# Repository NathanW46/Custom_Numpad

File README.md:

Custom numpad with 2 encoders and 18 Choc switches.
My first micro-electronics project.

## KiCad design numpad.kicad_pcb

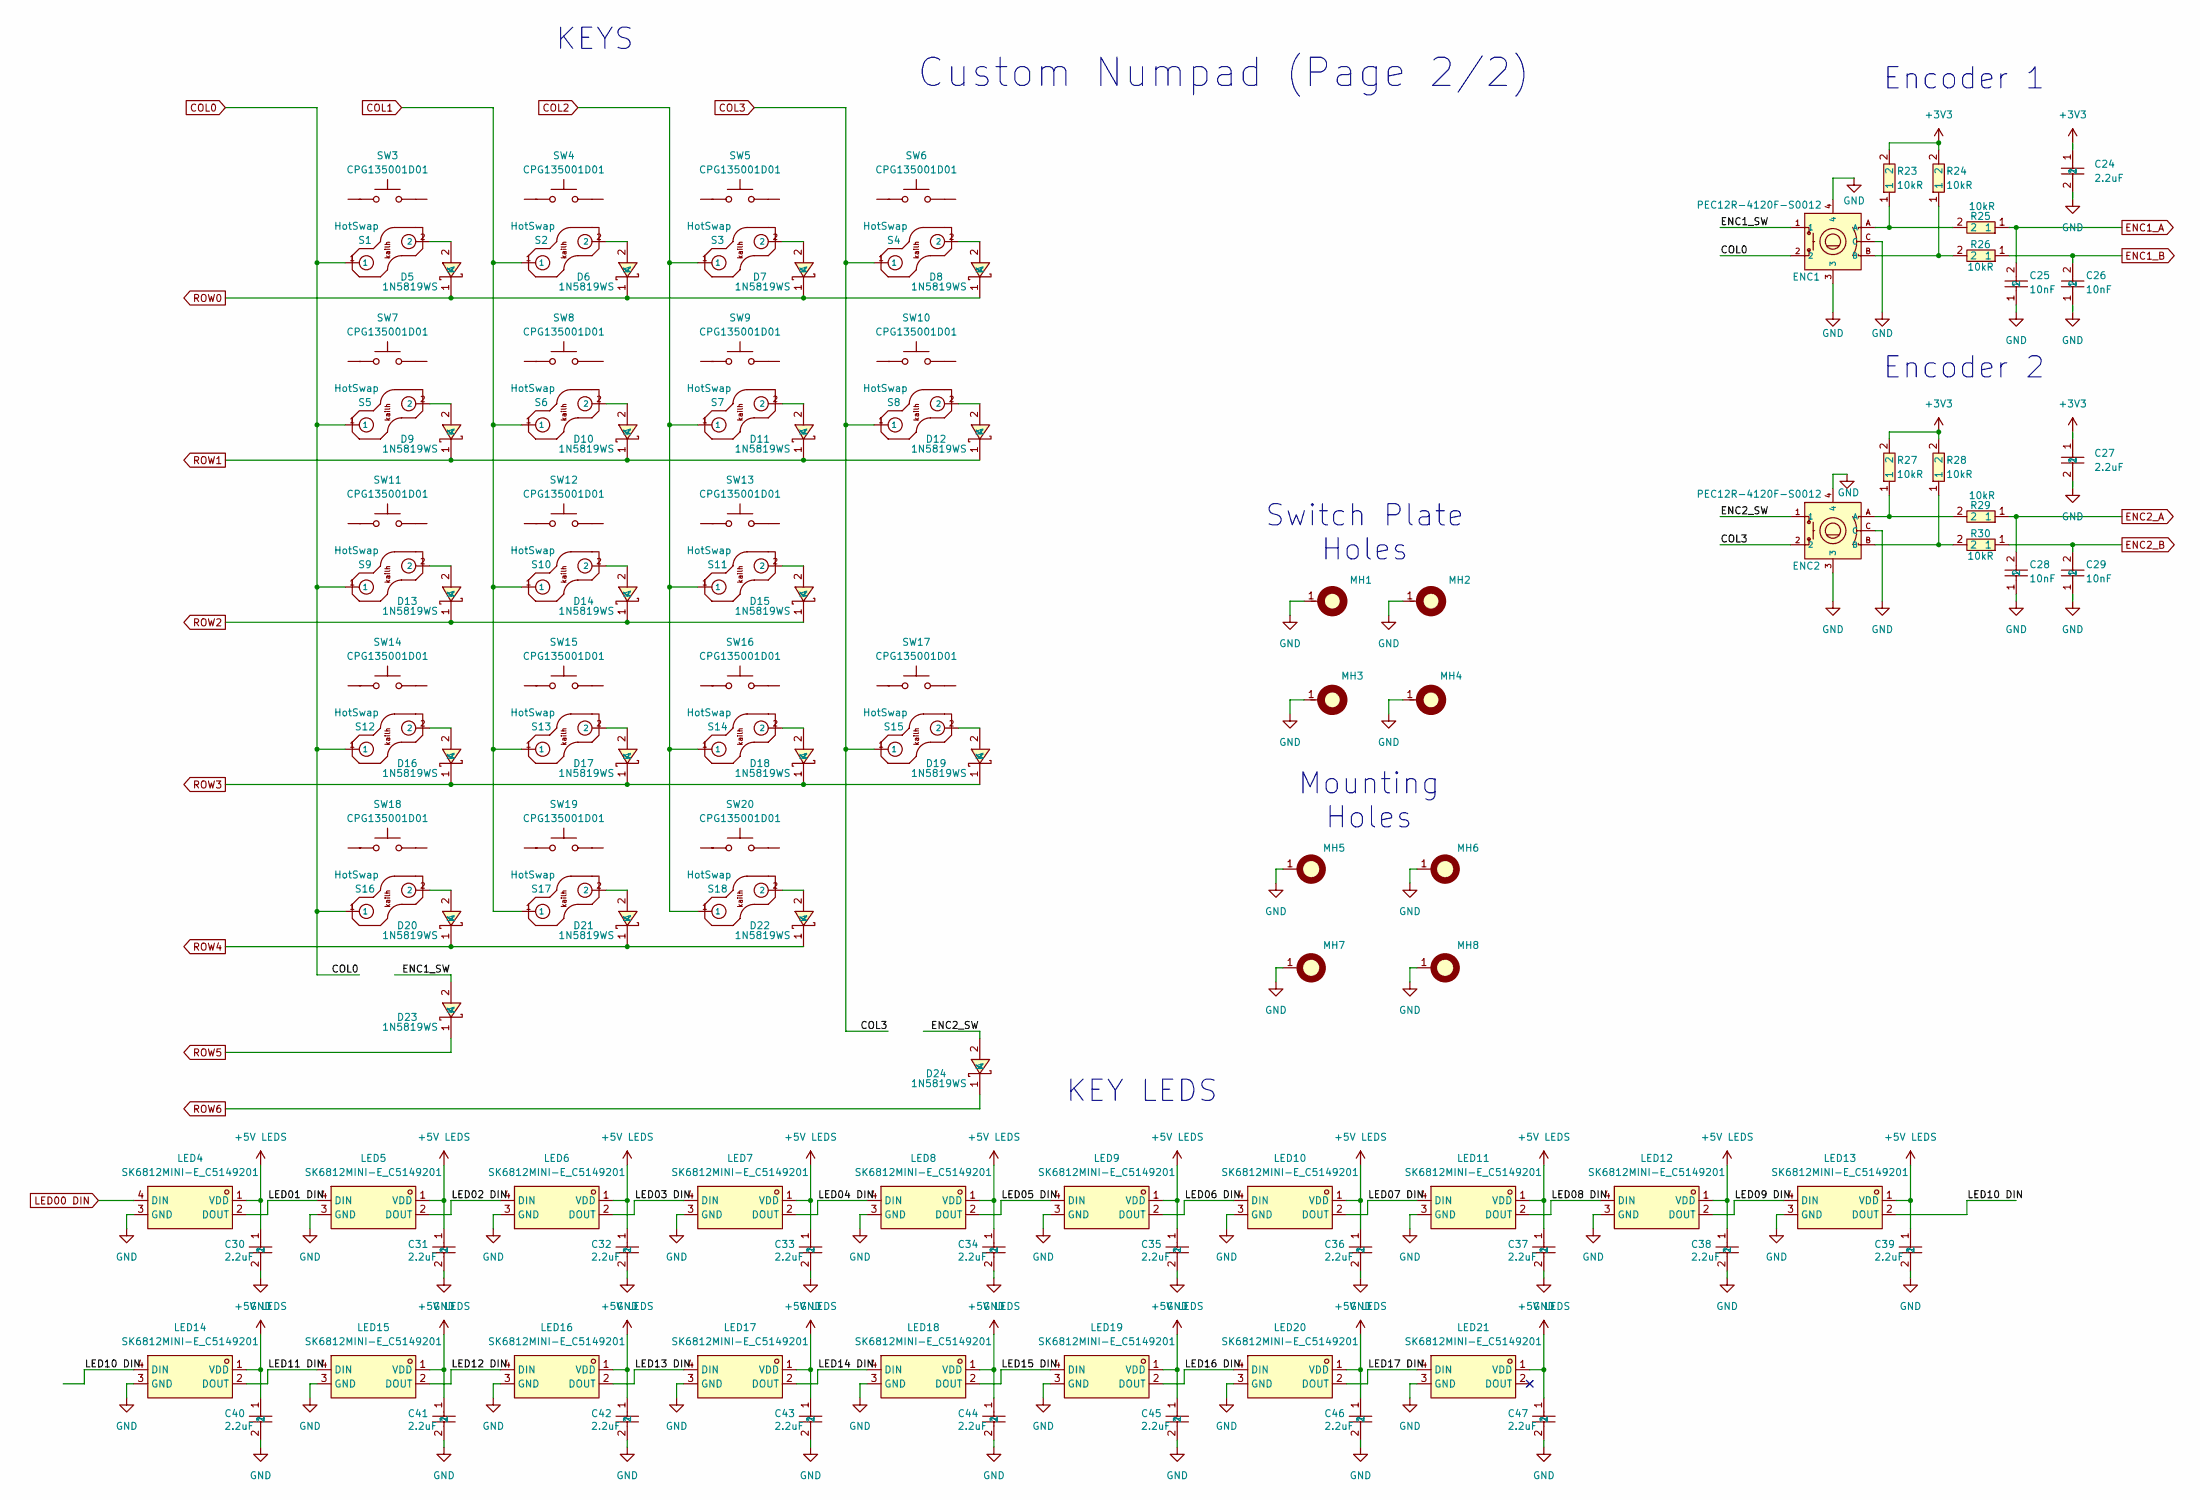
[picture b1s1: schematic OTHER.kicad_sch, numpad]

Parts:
C24, C27, C30, C31, C32, C33, C34, C35, C36, C37, C38, C39, C40, C41, C42, C43, C44, C45, C46, C47: 2.2uF; C0603; LCSC C12530
C25, C26, C28, C29: 10nF; C0603; LCSC C15195
D5, D6, D7, D8, D9, D10, D11, D12, D13, D14, D15, D16, D17, D18, D19, D20, D21, D22, D23, D24: 1N5819WS; SOD-323_L1.8-W1.3-LS2.5-RD; LCSC C191023
ENC1, ENC2: PEC12R-4120F-S0012; SW-TH_PEC12R-4120F-S0012; LCSC C143801
LED4, LED5, LED6, LED7, LED8, LED9, LED10, LED11, LED12, LED13, LED14, LED15, LED16, LED17, LED18, LED19, LED20, LED21: SK6812MINI-E_C5149201; LED-SMD_L3.2-W2.8-TR; LCSC C5149201
MH1, MH2, MH3, MH4: MH4X2.2MM
MH5, MH6, MH7, MH8: MH7.5X3.2MM
R23, R24, R25, R26, R27, R28, R29, R30: 10kR; R0603; LCSC C25744
S1, S2, S3, S4, S5, S6, S7, S8, S9, S10, S11, S12, S13, S14, S15, S16, S17, S18: HotSwap; Kailh_socket_PG1350; LCSC C5333465
SW3, SW4, SW5, SW6, SW7, SW8, SW9, SW10, SW11, SW12, SW13, SW14, SW15, SW16, SW17, SW18, SW19, SW20: CPG135001D01; LCSC C400229

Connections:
+3V3: C24.1, C27.1, R23.2, R24.2, R27.2, R28.2; also elsewhere on the board
+5V LEDS: C30.1, C31.1, C32.1, C33.1, C34.1, C35.1, C36.1, C37.1, C38.1, C39.1, C40.1, C41.1, C42.1, C43.1, C44.1, C45.1, C46.1, C47.1, LED4.1 (VDD), LED5.1 (VDD), LED6.1 (VDD), LED7.1 (VDD), LED8.1 (VDD), LED9.1 (VDD), LED10.1 (VDD), LED11.1 (VDD), LED12.1 (VDD), LED13.1 (VDD), LED14.1 (VDD), LED15.1 (VDD), LED16.1 (VDD), LED17.1 (VDD), LED18.1 (VDD), LED19.1 (VDD), LED20.1 (VDD), LED21.1 (VDD); also elsewhere on the board
/OTHER/ENC1_SW: D23.2 (A), ENC1.1
/OTHER/ENC2_SW: D24.2 (A), ENC2.1
/OTHER/LED01 DIN: LED4.2 (DOUT), LED5.4 (DIN)
/OTHER/LED02 DIN: LED5.2 (DOUT), LED6.4 (DIN)
/OTHER/LED03 DIN: LED6.2 (DOUT), LED7.4 (DIN)
/OTHER/LED04 DIN: LED7.2 (DOUT), LED8.4 (DIN)
/OTHER/LED05 DIN: LED8.2 (DOUT), LED9.4 (DIN)
/OTHER/LED06 DIN: LED9.2 (DOUT), LED10.4 (DIN)
/OTHER/LED07 DIN: LED10.2 (DOUT), LED11.4 (DIN)
/OTHER/LED08 DIN: LED11.2 (DOUT), LED12.4 (DIN)
/OTHER/LED09 DIN: LED12.2 (DOUT), LED13.4 (DIN)
/OTHER/LED10 DIN: LED13.2 (DOUT), LED14.4 (DIN)
/OTHER/LED11 DIN: LED14.2 (DOUT), LED15.4 (DIN)
/OTHER/LED12 DIN: LED15.2 (DOUT), LED16.4 (DIN)
/OTHER/LED13 DIN: LED16.2 (DOUT), LED17.4 (DIN)
/OTHER/LED14 DIN: LED17.2 (DOUT), LED18.4 (DIN)
/OTHER/LED15 DIN: LED18.2 (DOUT), LED19.4 (DIN)
/OTHER/LED16 DIN: LED19.2 (DOUT), LED20.4 (DIN)
/OTHER/LED17 DIN: LED20.2 (DOUT), LED21.4 (DIN)
COL0: ENC1.2, S1.1, S5.1, S9.1, S12.1, S16.1; also elsewhere on the board
COL1: S2.1, S6.1, S10.1, S13.1, S17.1; also elsewhere on the board
COL2: S3.1, S7.1, S11.1, S14.1, S18.1; also elsewhere on the board
COL3: ENC2.2, S4.1, S8.1, S15.1; also elsewhere on the board
ENC1_A: C25.2, R25.1; also elsewhere on the board
ENC1_B: C26.2, R26.1; also elsewhere on the board
ENC2_A: C28.2, R29.1; also elsewhere on the board
ENC2_B: C29.2, R30.1; also elsewhere on the board
GND: C24.2, C25.1, C26.1, C27.2, C28.1, C29.1, C30.2, C31.2, C32.2, C33.2, C34.2, C35.2, C36.2, C37.2, C38.2, C39.2, C40.2, C41.2, C42.2, C43.2, C44.2, C45.2, C46.2, C47.2, ENC1.3, ENC1.4, ENC1.C, ENC2.3, ENC2.4, ENC2.C, LED4.3 (GND), LED5.3 (GND), LED6.3 (GND), LED7.3 (GND), LED8.3 (GND), LED9.3 (GND), LED10.3 (GND), LED11.3 (GND), LED12.3 (GND), LED13.3 (GND), LED14.3 (GND), LED15.3 (GND), LED16.3 (GND), LED17.3 (GND), LED18.3 (GND), LED19.3 (GND), LED20.3 (GND), LED21.3 (GND), MH1.1, MH2.1, MH3.1, MH4.1, MH5.1, MH6.1, MH7.1, MH8.1; also elsewhere on the board
LED00 DIN: LED4.4 (DIN); also elsewhere on the board
unnamed: D5.2 (A), S1.2
unnamed: D6.2 (A), S2.2
unnamed: D7.2 (A), S3.2
unnamed: D8.2 (A), S4.2
unnamed: D9.2 (A), S5.2
unnamed: D10.2 (A), S6.2
unnamed: D11.2 (A), S7.2
unnamed: D12.2 (A), S8.2
unnamed: D13.2 (A), S9.2
unnamed: D14.2 (A), S10.2
unnamed: D15.2 (A), S11.2
unnamed: D16.2 (A), S12.2
unnamed: D17.2 (A), S13.2
unnamed: D18.2 (A), S14.2
unnamed: D19.2 (A), S15.2
unnamed: D20.2 (A), S16.2
unnamed: D21.2 (A), S17.2
unnamed: D22.2 (A), S18.2
unnamed: ENC1.A, R23.1, R25.2
unnamed: ENC1.B, R24.1, R26.2
unnamed: ENC2.A, R27.1, R29.2
unnamed: ENC2.B, R28.1, R30.2
ROW0: D5.1 (K), D6.1 (K), D7.1 (K), D8.1 (K); also elsewhere on the board
ROW1: D9.1 (K), D10.1 (K), D11.1 (K), D12.1 (K); also elsewhere on the board
ROW2: D13.1 (K), D14.1 (K), D15.1 (K); also elsewhere on the board
ROW3: D16.1 (K), D17.1 (K), D18.1 (K), D19.1 (K); also elsewhere on the board
ROW4: D20.1 (K), D21.1 (K), D22.1 (K); also elsewhere on the board
ROW5: D23.1 (K); also elsewhere on the board
ROW6: D24.1 (K); also elsewhere on the board

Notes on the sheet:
Custom Numpad (Page 2/2)
Encoder 2
KEYS
Mounting Holes
Encoder 1
KEY LEDS
Switch Plate Holes

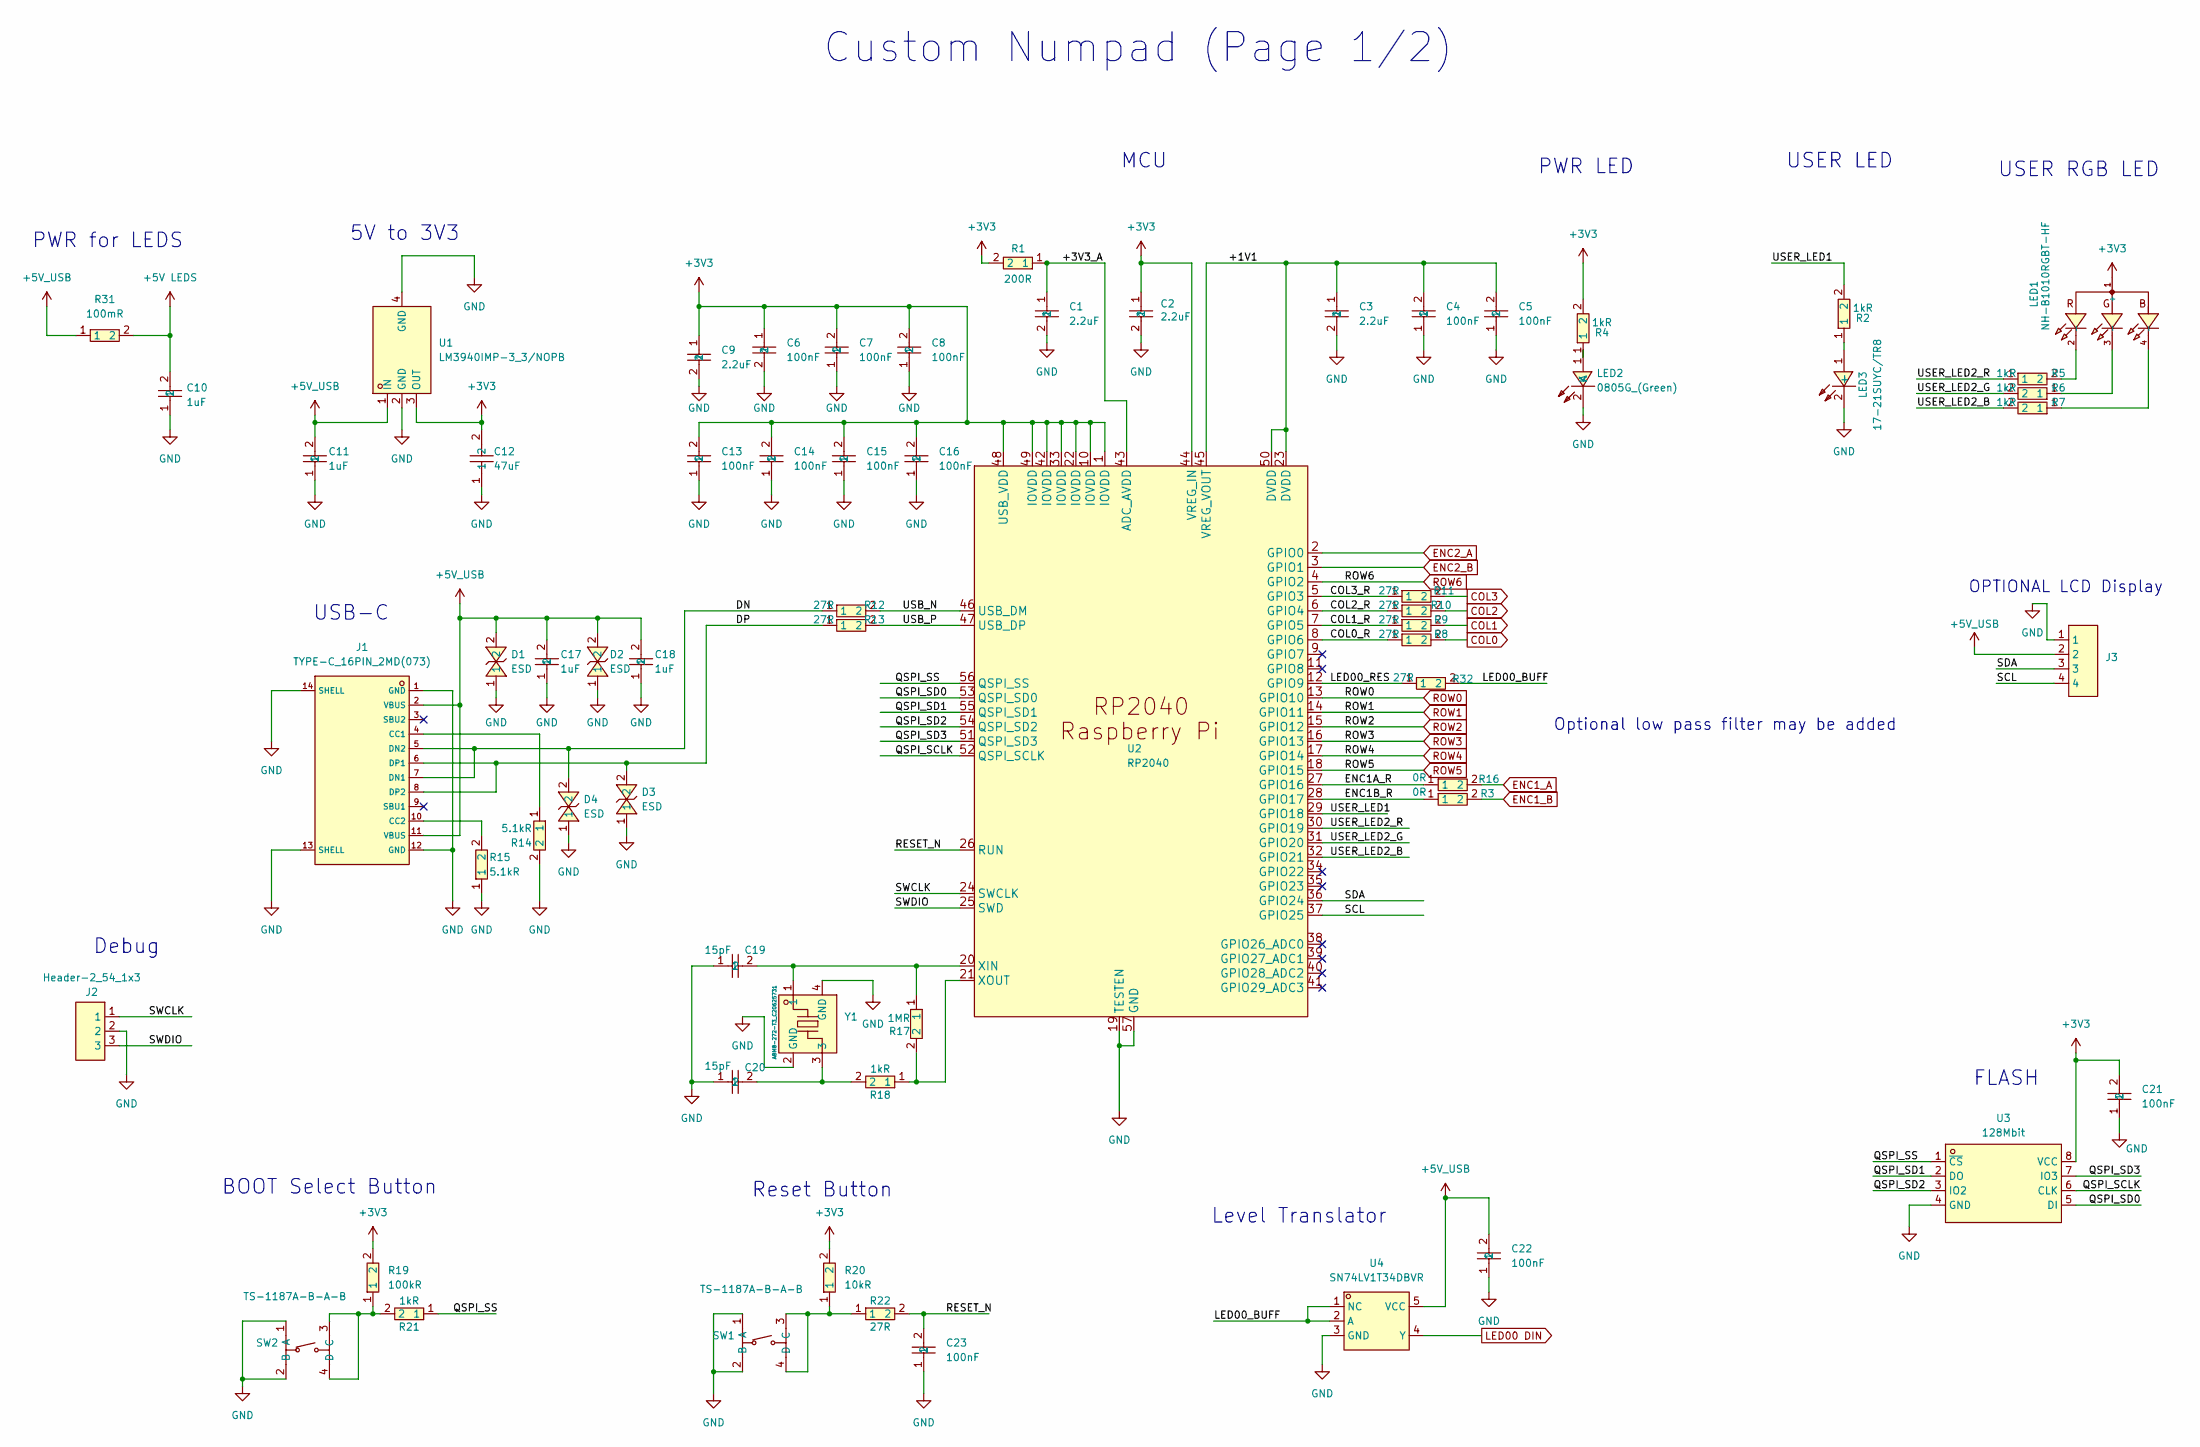
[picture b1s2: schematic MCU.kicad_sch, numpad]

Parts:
C1, C2, C3, C9: 2.2uF; C0603; LCSC C12530
C4, C5, C6, C7, C8, C13, C14, C15, C16, C21, C22, C23: 100nF; C0603; LCSC C160831
C10, C11, C18: 1uF; C0603; LCSC C52923
C12: 47uF; C1206; LCSC C96123
C17: 1uF; C0603; LCSC Part C1592
C19, C20: 15pF; C0603; LCSC C86285
D1, D2, D3, D4: ESD; D0402-BI; LCSC C1973257
J1: TYPE-C_16PIN_2MD(073); USB-C-SMD_TYPE-C-6PIN-2MD-073; LCSC C2765186
J2: Header-2_54_1x3; HDR-TH_3P-P2.54-V-M-1; LCSC C49257
J3: PinHeader_1x04_P2.54mm_Vertical
LED1: NH-B1010RGBT-HF; LED-ARRAY-SMD_4P-L1.0-W1.0-TR_NH-B1010RGBT; LCSC C2874113
LED2: 0805G_(Green); LED0805-R-RD; LCSC C2297
LED3: 17-21SUYC/TR8; LED0805-R-RD; LCSC C2296
R1: 200R; R0603; LCSC C25087
R2, R4, R5, R6, R7, R18, R21: 1kR; R0603; LCSC C11702
R3, R16: 0R; R0603; LCSC Part C21189
R8, R9, R10, R11, R12, R13, R22, R32: 27R; R0603; LCSC C25100
R14, R15: 5.1kR; R0603; LCSC C25905
R17: 1MR; R0603; LCSC C26083
R19: 100kR; R0603; LCSC C25741
R20: 10kR; R0603; LCSC C25744
R31: 100mR; R1206; LCSC C25334
SW1, SW2: TS-1187A-B-A-B; SW-SMD_4P-L5.1-W5.1-P3.70-LS6.5-TL_H1.5; LCSC C318884
U1: LM3940IMP-3_3/NOPB; SOT-223_L6.5-W3.5-P2.30-LS7.0-BR; LCSC C140319
U2: RP2040; LQFN-56_L7.0-W7.0-P0.4-EP; LCSC C2040
U3: 128Mbit; SOIC-8_L5.3-W5.3-P1.27-LS8.0-BL; LCSC C97521
U4: SN74LV1T34DBVR; SOT-23-5_L2.9-W1.6-P0.95-LS2.8-BR; LCSC Part C100024
Y1: ABM8-272-T3_C20625731; CRYSTAL-SMD_4P-L3.2-W2.5-BL; LCSC C20625731

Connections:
+3V3: C2.1, C6.1, C7.2, C8.2, C9.1, C12.2, C13.2, C14.2, C15.2, C16.2, C21.2, LED1.1 (+), R1.2, R4.2, R19.2, R20.2, U1.3 (OUT), U2.1 (IOVDD), U2.10 (IOVDD), U2.22 (IOVDD), U2.33 (IOVDD), U2.42 (IOVDD), U2.44 (VREG_IN), U2.48 (USB_VDD), U2.49 (IOVDD), U3.8 (VCC); also elsewhere on the board
+5V LEDS: C10.2, R31.2; also elsewhere on the board
+5V_USB: C11.2, C17.2, C18.2, C22.2, D1.2, D2.2, J1.2 (VBUS), J1.11 (VBUS), J3.2, R31.1, U1.1 (IN), U4.5 (VCC)
/MCU/+1V1: C3.1, C4.2, C5.2, U2.23 (DVDD), U2.45 (VREG_VOUT), U2.50 (DVDD)
/MCU/+3V3_A: C1.1, R1.1, U2.43 (ADC_AVDD)
/MCU/COL0_R: R8.1, U2.8 (GPIO6)
/MCU/COL1_R: R9.1, U2.7 (GPIO5)
/MCU/COL2_R: R10.1, U2.6 (GPIO4)
/MCU/COL3_R: R11.1, U2.5 (GPIO3)
/MCU/DN: D4.2, J1.5 (DN2), J1.7 (DN1), R12.1
/MCU/DP: D3.2, J1.6 (DP1), J1.8 (DP2), R13.1
/MCU/ENC1A_R: R16.1, U2.27 (GPIO16)
/MCU/ENC1B_R: R3.1, U2.28 (GPIO17)
/MCU/LED00_BUFF: R32.2, U4.1 (NC), U4.2 (A)
/MCU/LED00_RES: R32.1, U2.12 (GPIO9)
/MCU/QSPI_SCLK: U2.52 (QSPI_SCLK), U3.6 (CLK)
/MCU/QSPI_SD0: U2.53 (QSPI_SD0), U3.5 (DI)
/MCU/QSPI_SD1: U2.55 (QSPI_SD1), U3.2 (DO)
/MCU/QSPI_SD2: U2.54 (QSPI_SD2), U3.3 (IO2)
/MCU/QSPI_SD3: U2.51 (QSPI_SD3), U3.7 (IO3)
/MCU/QSPI_SS: R21.1, U2.56 (QSPI_SS), U3.1 (~CS)
/MCU/RESET_N: C23.2, R22.2, U2.26 (RUN)
/MCU/SCL: J3.4, U2.37 (GPIO25)
/MCU/SDA: J3.3, U2.36 (GPIO24)
/MCU/SWCLK: J2.1, U2.24 (SWCLK)
/MCU/SWDIO: J2.3, U2.25 (SWD)
/MCU/USB_N: R12.2, U2.46 (USB_DM)
/MCU/USB_P: R13.2, U2.47 (USB_DP)
/MCU/USER_LED1: R2.2, U2.29 (GPIO18)
/MCU/USER_LED2_B: R7.2, U2.32 (GPIO21)
/MCU/USER_LED2_G: R6.2, U2.31 (GPIO20)
/MCU/USER_LED2_R: R5.1, U2.30 (GPIO19)
COL0: R8.2; also elsewhere on the board
COL1: R9.2; also elsewhere on the board
COL2: R10.2; also elsewhere on the board
COL3: R11.2; also elsewhere on the board
ENC1_A: R16.2; also elsewhere on the board
ENC1_B: R3.2; also elsewhere on the board
ENC2_A: U2.2 (GPIO0); also elsewhere on the board
ENC2_B: U2.3 (GPIO1); also elsewhere on the board
GND: C1.2, C2.2, C3.2, C4.1, C5.1, C6.2, C7.1, C8.1, C9.2, C10.1, C11.1, C12.1, C13.1, C14.1, C15.1, C16.1, C17.1, C18.1, C19.1, C20.1, C21.1, C22.1, C23.1, D1.1, D2.1, D3.1, D4.1, J1.1 (GND), J1.12 (GND), J1.13 (SHELL), J1.14 (SHELL), J2.2, J3.1, LED2.2 (K), LED3.2 (-), R14.2, R15.1, SW1.1 (A), SW1.2 (B), SW2.1 (A), SW2.2 (B), U1.2 (GND), U1.4 (GND), U2.19 (TESTEN), U2.57 (GND), U3.4 (GND), U4.3 (GND), Y1.2 (GND), Y1.4 (GND); also elsewhere on the board
LED00 DIN: U4.4 (Y); also elsewhere on the board
unnamed: C20.2, R18.2, Y1.3
unnamed: J1.4 (CC1), R14.1
unnamed: J1.10 (CC2), R15.2
unnamed: LED1.2 (-), R5.2
unnamed: LED1.3 (-), R6.1
unnamed: LED1.4 (-), R7.1
unnamed: LED2.1 (A), R4.1
unnamed: LED3.1 (+), R2.1
unnamed: R20.1, R22.1, SW1.3 (C), SW1.4 (D)
unnamed: R19.1, R21.2, SW2.3 (C), SW2.4 (D)
unnamed: C19.2, R17.1, U2.20 (XIN), Y1.1
unnamed: R17.2, R18.1, U2.21 (XOUT)
ROW0: U2.13 (GPIO10); also elsewhere on the board
ROW1: U2.14 (GPIO11); also elsewhere on the board
ROW2: U2.15 (GPIO12); also elsewhere on the board
ROW3: U2.16 (GPIO13); also elsewhere on the board
ROW4: U2.17 (GPIO14); also elsewhere on the board
ROW5: U2.18 (GPIO15); also elsewhere on the board
ROW6: U2.4 (GPIO2); also elsewhere on the board

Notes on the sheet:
Optional low pass filter may be added
OPTIONAL LCD Display
Reset Button
Custom Numpad (Page 1/2)
USER LED
MCU
BOOT Select Button
USB-C
Debug
FLASH
5V to 3V3
USER RGB LED
PWR for LEDS
Level Translator
PWR LED

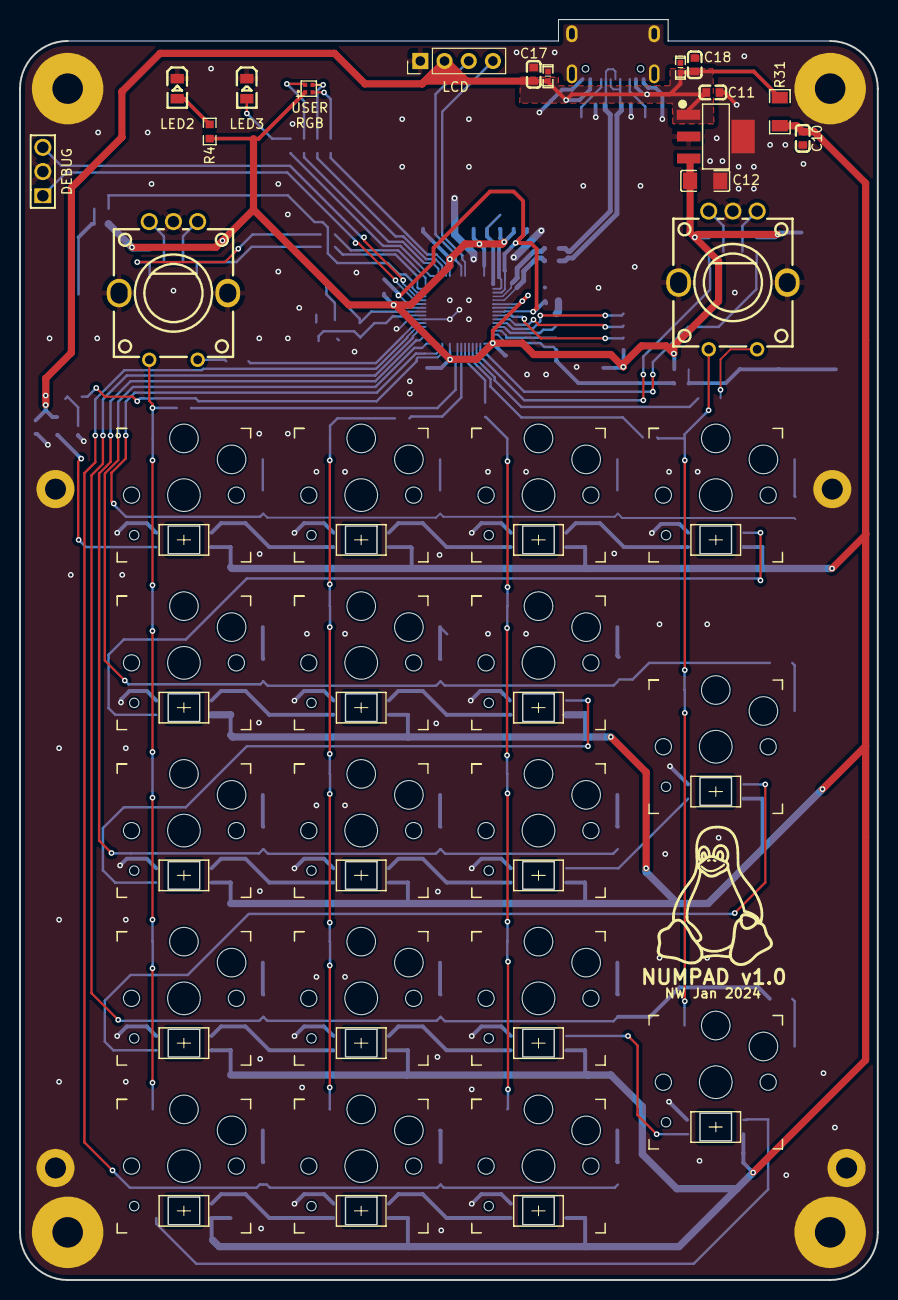
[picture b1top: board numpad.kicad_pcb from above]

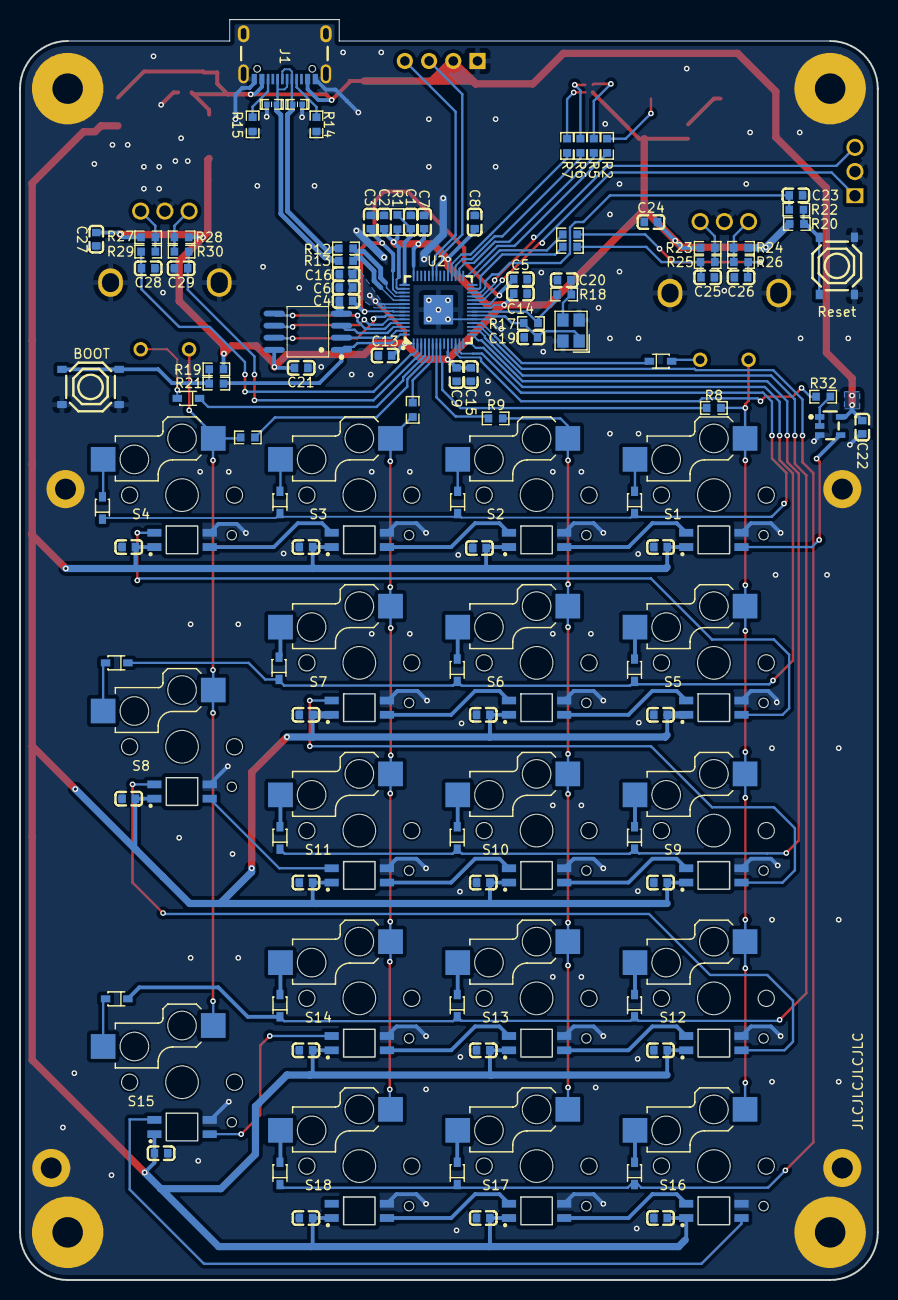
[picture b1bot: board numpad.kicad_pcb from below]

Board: 2 copper layers, 90.0 x 132.2 mm, 162 parts (119 on the bottom side), 102 nets.

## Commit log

2025-01-13 repo creation
2025-01-13 rm backups
2025-01-13 ignore backups
2025-01-13 Added silkscreen details
2025-01-13 deleted .lcm
2025-01-13 pdf veiws
2025-01-14 pcb finished + production files
